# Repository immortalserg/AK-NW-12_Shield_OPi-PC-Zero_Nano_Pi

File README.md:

# AK-NW-12_Shield_OPi-PC-Zero_Nano_Pi

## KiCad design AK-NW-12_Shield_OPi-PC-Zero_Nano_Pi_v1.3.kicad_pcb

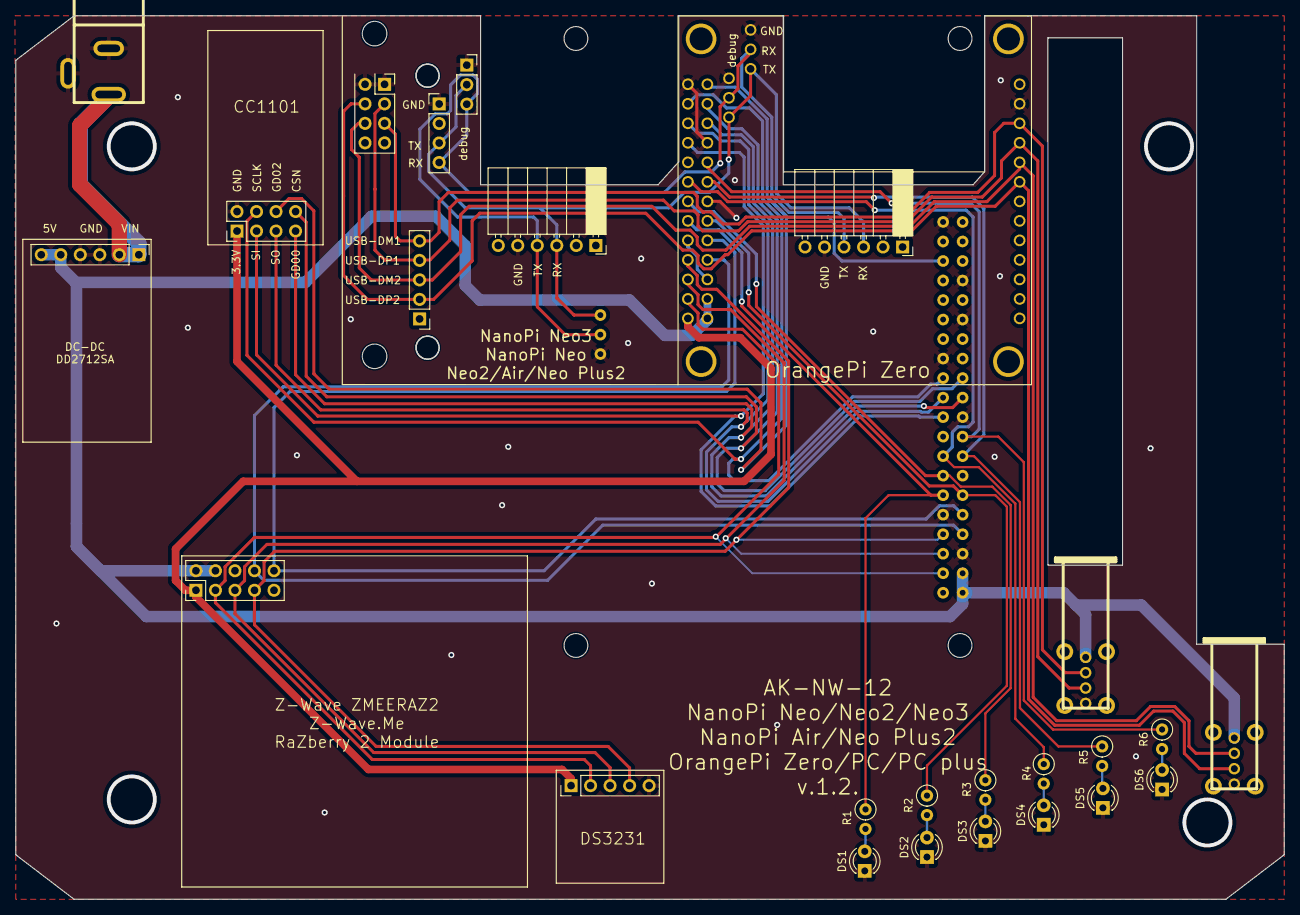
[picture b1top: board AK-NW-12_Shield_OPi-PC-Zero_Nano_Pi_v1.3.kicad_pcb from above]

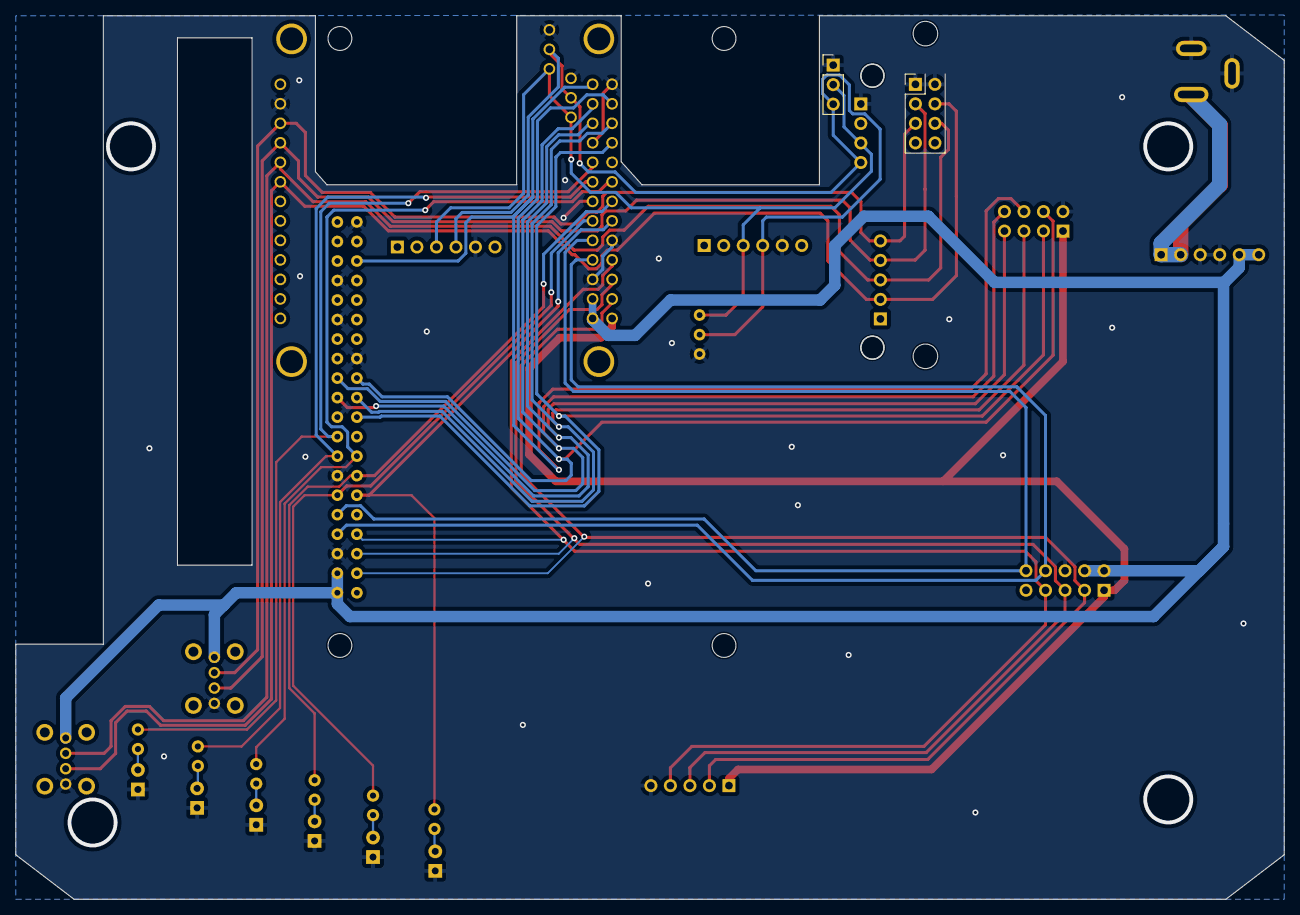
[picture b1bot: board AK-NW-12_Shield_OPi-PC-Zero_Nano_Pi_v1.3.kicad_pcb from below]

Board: 2 copper layers, 165.1 x 115.0 mm, 25 parts (3 on the bottom side), 33 nets.

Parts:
DS1, DS2, DS3, DS4, DS5, DS6: LED; LED_D3.0mm
H1, H2: MountingHole; MountingHole_3mm
J1: Conn_01x02; dc_socket
J2: Conn_01x06; PinHeader_1x06_P2.54mm_Vertical
J3, J4: USB_2; conn_usb_A-vert
J5: Conn_02x04_Odd_Even; PinHeader_2x04_P2.54mm_Vertical
J6, J7: Conn_01x06; PinSocket_1x06_P2.54mm_Horizontal
P1: CONN_01X05; PinHeader_1x05_P2.54mm_Vertical
P2: CONN_02X06; PinHeader_2x05_P2.54mm_Vertical
R1, R2, R3, R4, R5, R6: R; R_Axial_DIN0207_L6.3mm_D2.5mm_P2.54mm_Vertical
U1: orange_pi_zero; orangepi-zero
U3: OrangePiPC

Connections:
3.3V: J5.1, P1.1, P2.1, U1.101 (3.3V)
5V: J2.5, J2.6, J3.1, J4.1, P2.2, P2.4, U1.102 (5V), U1.104 (5V), U3.2 (VCC-5V), U3.4 (VCC-5V)
12V: J1.3, J2.1, J2.2
CSN: J5.8, U1.124 (PI1_CS_/_PA13), U3.24 (PC3 (NAND_CE1/SPI0_CS))
GD00: J5.7, U1.122 (UART2_RTS_/_PA02), U3.22 (PA2 (UART2_RTS/JTAG_DO0/PA_EINT2))
GD02: J5.6, U1.126 (SIM_DET/PA_EINT10_/_PA10), U3.35 (PA10 (SIM_DET/PA_EINT10))
GND: DS1.1 (K), DS2.1 (K), DS3.1 (K), DS4.1 (K), DS5.1 (K), DS6.1 (K), J1.1, J1.2, J2.3, J2.4, J3.4, J4.4, J5.2, J6.5, J7.5, P1.5, P2.6, U1.2 (GND), U1.106 (GND), U1.109 (GND), U1.114 (GND), U1.120 (GND), U1.125 (GND), U1.201 (GND), U3.6 (GND), U3.9 (GND), U3.14 (GND), U3.20 (GND), U3.25 (GND), U3.30 (GND), U3.34 (GND), U3.39 (GND), U3.201 (GND)
LED1: R1.1, U1.111 (UART2_RX_/_PA01), U3.11 (PA1 (UART2_RX/JTAG_CK0/PA_EINT1))
LED2: R2.1, U1.112 (SIM_CLK/PA_EINT7_/_PA07), U3.12 (PD14(RGMII_NULL/MII_TXERR/RMII_NULL))
LED3: R3.1, U1.113 (UART2_TX_/_PA00), U3.13 (PA0 (UART2_TX/JTAG_MS0/PA_EINT0))
LED4: R4.1, U1.115 (_UART2_CTS_/_PA03), U3.15 (PA3 (UART2_CTS/JTAG_DI0/PA_EINT3))
LED5: R5.1, U1.116 (TWI1-SDA_/_PA19), U3.16 (PC4 (NAND_CE0))
LED6: R6.1, U1.118 (TWI1-SCK_/_PA18), U3.18 (PC7 (NAND_RB1))
unnamed: DS2.2 (A), R2.2
unnamed: DS3.2 (A), R3.2
unnamed: DS4.2 (A), R4.2
unnamed: DS5.2 (A), R5.2
unnamed: DS6.2 (A), R6.2
unnamed: DS1.2 (A), R1.2
unnamed: J3.2, U1.3 (USB-DM2)
unnamed: J4.2, U1.5 (USB-DM3)
unnamed: J3.3, U1.4 (USB-DP2)
unnamed: J4.3, U1.6 (USB-DP3)
PWM1: P1.4, P2.7, U1.107 (PWM1_/_PA06), U3.7 (PA6 (SIM_PWREN/PWM1/PA_EINT6))
RX: J6.4, J7.4, U1.202 (RX), U3.202 (UART0_RX)
SCK: P1.3, P2.5, U1.105 (TWI0_SCK_/_PA11), U3.5 (PA11 (TWI0-SCK/DI_TX/EINT11))
SCLK: J5.4, U1.123 (SPI1_CLK_/_PA14), U3.23 (PC2 (NAND_CLE/SPI0_CLK))
SDA: P1.2, P2.3, U1.103 (TWI0_SDA_/_PA12), U3.3 (PA12 (TWI0-SDA/DI_RX/EINT12))
SI: J5.3, U1.119 (SPI1_MOSI_/_PA15), U3.19 (PC0 (NAND_WE/SPI0_MOSI))
SO: J5.5, U1.121 (SPI1_MISO_/_PA16), U3.21 (PC1 (NAND_ALE/SPI0_MISO))
TX: J6.3, J7.3, U1.203 (TX), U3.203 (UART0_TX)
UART_RX: P2.10, U1.110 (UART1_RX_/_PG07), U3.10 (PA14 (SPI1_CLK/UART3_RX/PA_EINT14))
UART_TX: P2.8, U1.108 (UART1_TX_/_PG06), U3.8 (PA13 (SPI1_CS/UART3_TX/PA_EINT13))
